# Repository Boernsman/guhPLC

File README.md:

# nymea PLC
The purpose was to design a smart home server that runns guhIO and is especially fittet to the needs of single-family house builders. It is the central switching unit that can be mounted into the electrical cabinet.

Please note: guhPLC is the abbreviation for 'guh' programmable logic controller. The smart home server has no powerline interface yet.

The layout is not yet tested - no warranty for functionality

	Copyright guh GmbH 2015-2019.

	This documentation describes Open Hardware and is licensed under the CERN OHL v. 1.2.

	You may redistribute and modify this documentation under the terms of the CERN OHL v.1.2. (http://ohwr.org/cernohl).
	
	This documentation is distributed WITHOUT ANY EXPRESS OR IMPLIED WARRANTY, INCLUDING OF MERCHANTABILITY,
	SATISFACTORY QUALITY AND FITNESS FOR A PARTICULAR PURPOSE. Please see the CERN OHL v.1.2 for applicable conditions

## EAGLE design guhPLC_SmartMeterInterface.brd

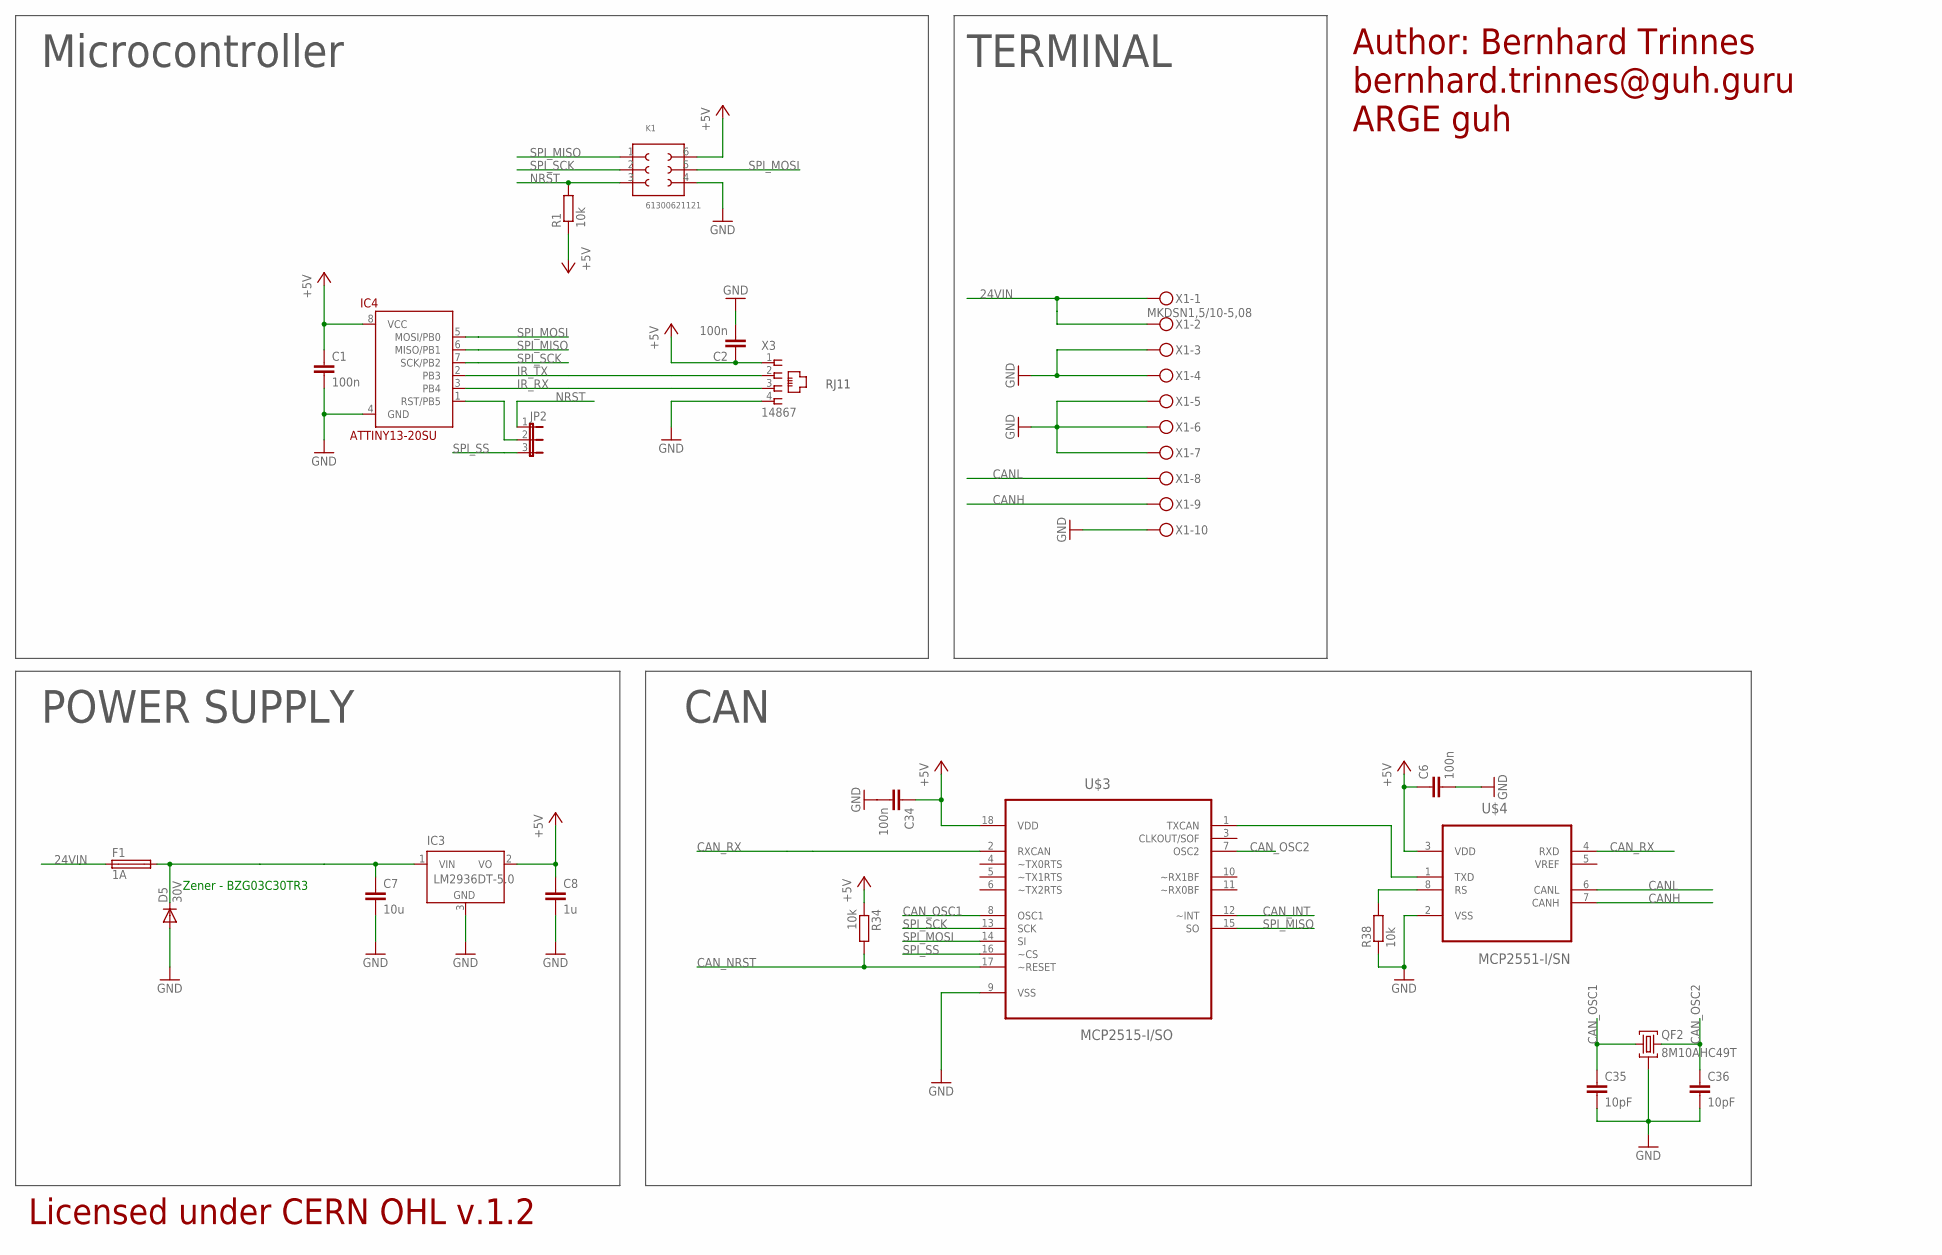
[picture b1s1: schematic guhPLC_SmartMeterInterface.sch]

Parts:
C1, C2, C6, C34: 100n; C0603
C7: 10u; C1206
C8: 1u; C0603
C35, C36: 10pF; C0603
D5: 30V; DO214AC
F1: 1A; LITTLEFUSE
IC3: LM2936DT-5.0; TO252
IC4: ATTINY13-20SU; SOIC8
JP2: JP2E; JP2
K1: 61300621121
QF2: 8M10AHC49T; HC49U
R1, R34, R38: 10k; R0603
U$3: MCP2515-I/SO; SOIC127P1034X264-18N
U$4: MCP2551-I/SN; SOIC127P600X175-8N
X1: MKDSN1,5/10-5,08
X3: 14867

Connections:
24VIN: F1.1, X1.1, X1.2
+5V: C1.1, C2.1, C6.1, C8.1, C34.1, IC3.2 (VO), IC4.8 (VCC), K1.6, R1.1, R34.1, U$3.18 (VDD), U$4.3 (VDD), X3.1
CANH: U$4.7 (CANH), X1.9
CANL: U$4.6 (CANL), X1.8
CAN_INT: U$3.12 (~INT)
CAN_NRST: R34.2, U$3.17 (~RESET)
CAN_OSC1: C35.1, QF2.1, U$3.8 (OSC1)
CAN_OSC2: C36.1, QF2.3, U$3.7 (OSC2)
CAN_RX: U$3.2 (RXCAN), U$4.4 (RXD)
GND: C1.2, C2.2, C6.2, C7.2, C8.2, C34.2, C35.2, C36.2, D5.A, IC3.3 (GND), IC4.4 (GND), K1.4, QF2.2, R38.1, U$3.9 (VSS), U$4.2 (VSS), X1.3, X1.4, X1.5, X1.6, X1.7, X1.10, X3.4
IR_RX: IC4.3 (PB4), X3.3
IR_TX: IC4.2 (PB3), X3.2
unnamed: IC4.1 (RST/PB5), JP2.2
unnamed: U$3.1 (TXCAN), U$4.1 (TXD)
unnamed: R38.2, U$4.8 (RS)
NRST: JP2.1, K1.3, R1.2
SPI_MISO: IC4.6 (MISO/PB1), K1.1, U$3.15 (SO)
SPI_MOSI: IC4.5 (MOSI/PB0), K1.5, U$3.14 (SI)
SPI_SCK: IC4.7 (SCK/PB2), K1.2, U$3.13 (SCK)
SPI_SS: JP2.3, U$3.16 (~CS)
VCC: C7.1, D5.C, F1.2, IC3.1 (VIN)

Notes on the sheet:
CAN
POWER SUPPLY
Microcontroller
TERMINAL
Author: Bernhard Trinnes
bernhard.trinnes@guh.guru
ARGE guh
Licensed under CERN OHL v.1.2
Zener - BZG03C30TR3
RJ11

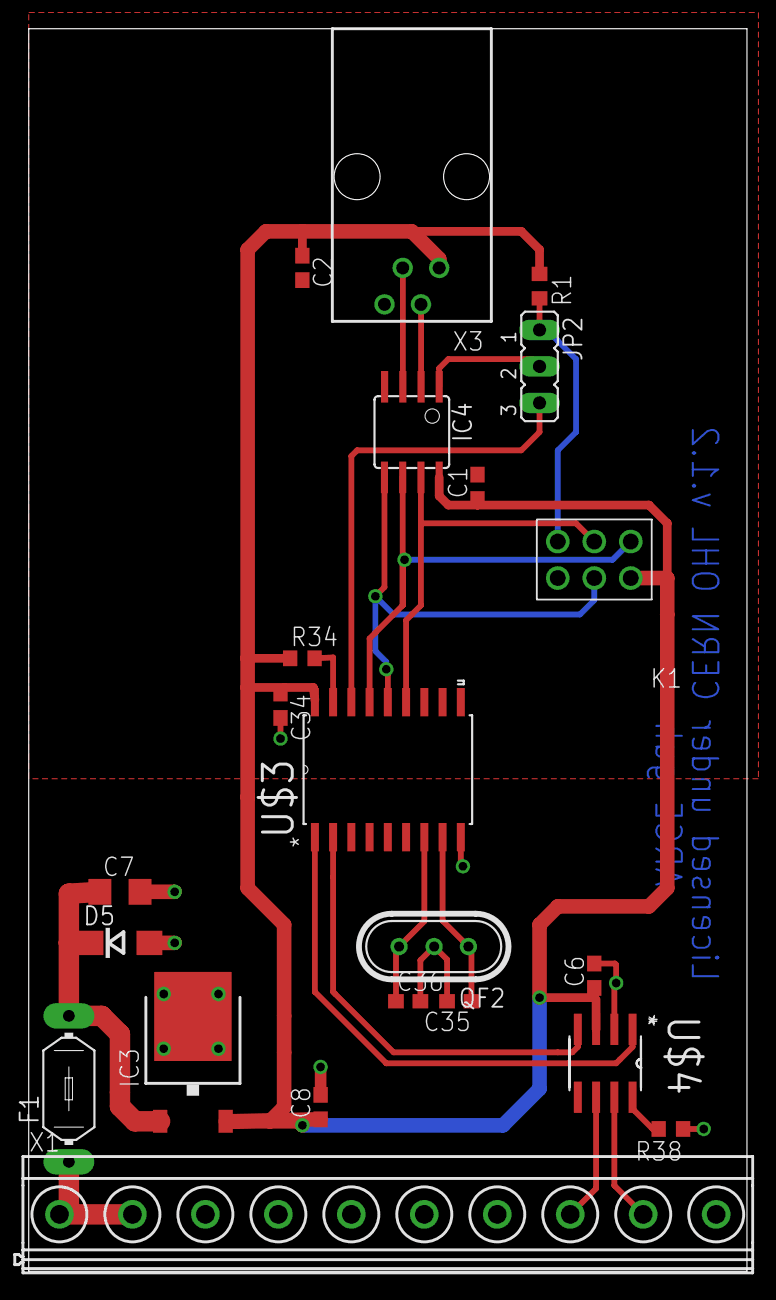
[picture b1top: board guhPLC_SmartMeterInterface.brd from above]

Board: 2 copper layers, 50.0 x 86.5 mm, 22 parts (0 on the bottom side), 20 nets.

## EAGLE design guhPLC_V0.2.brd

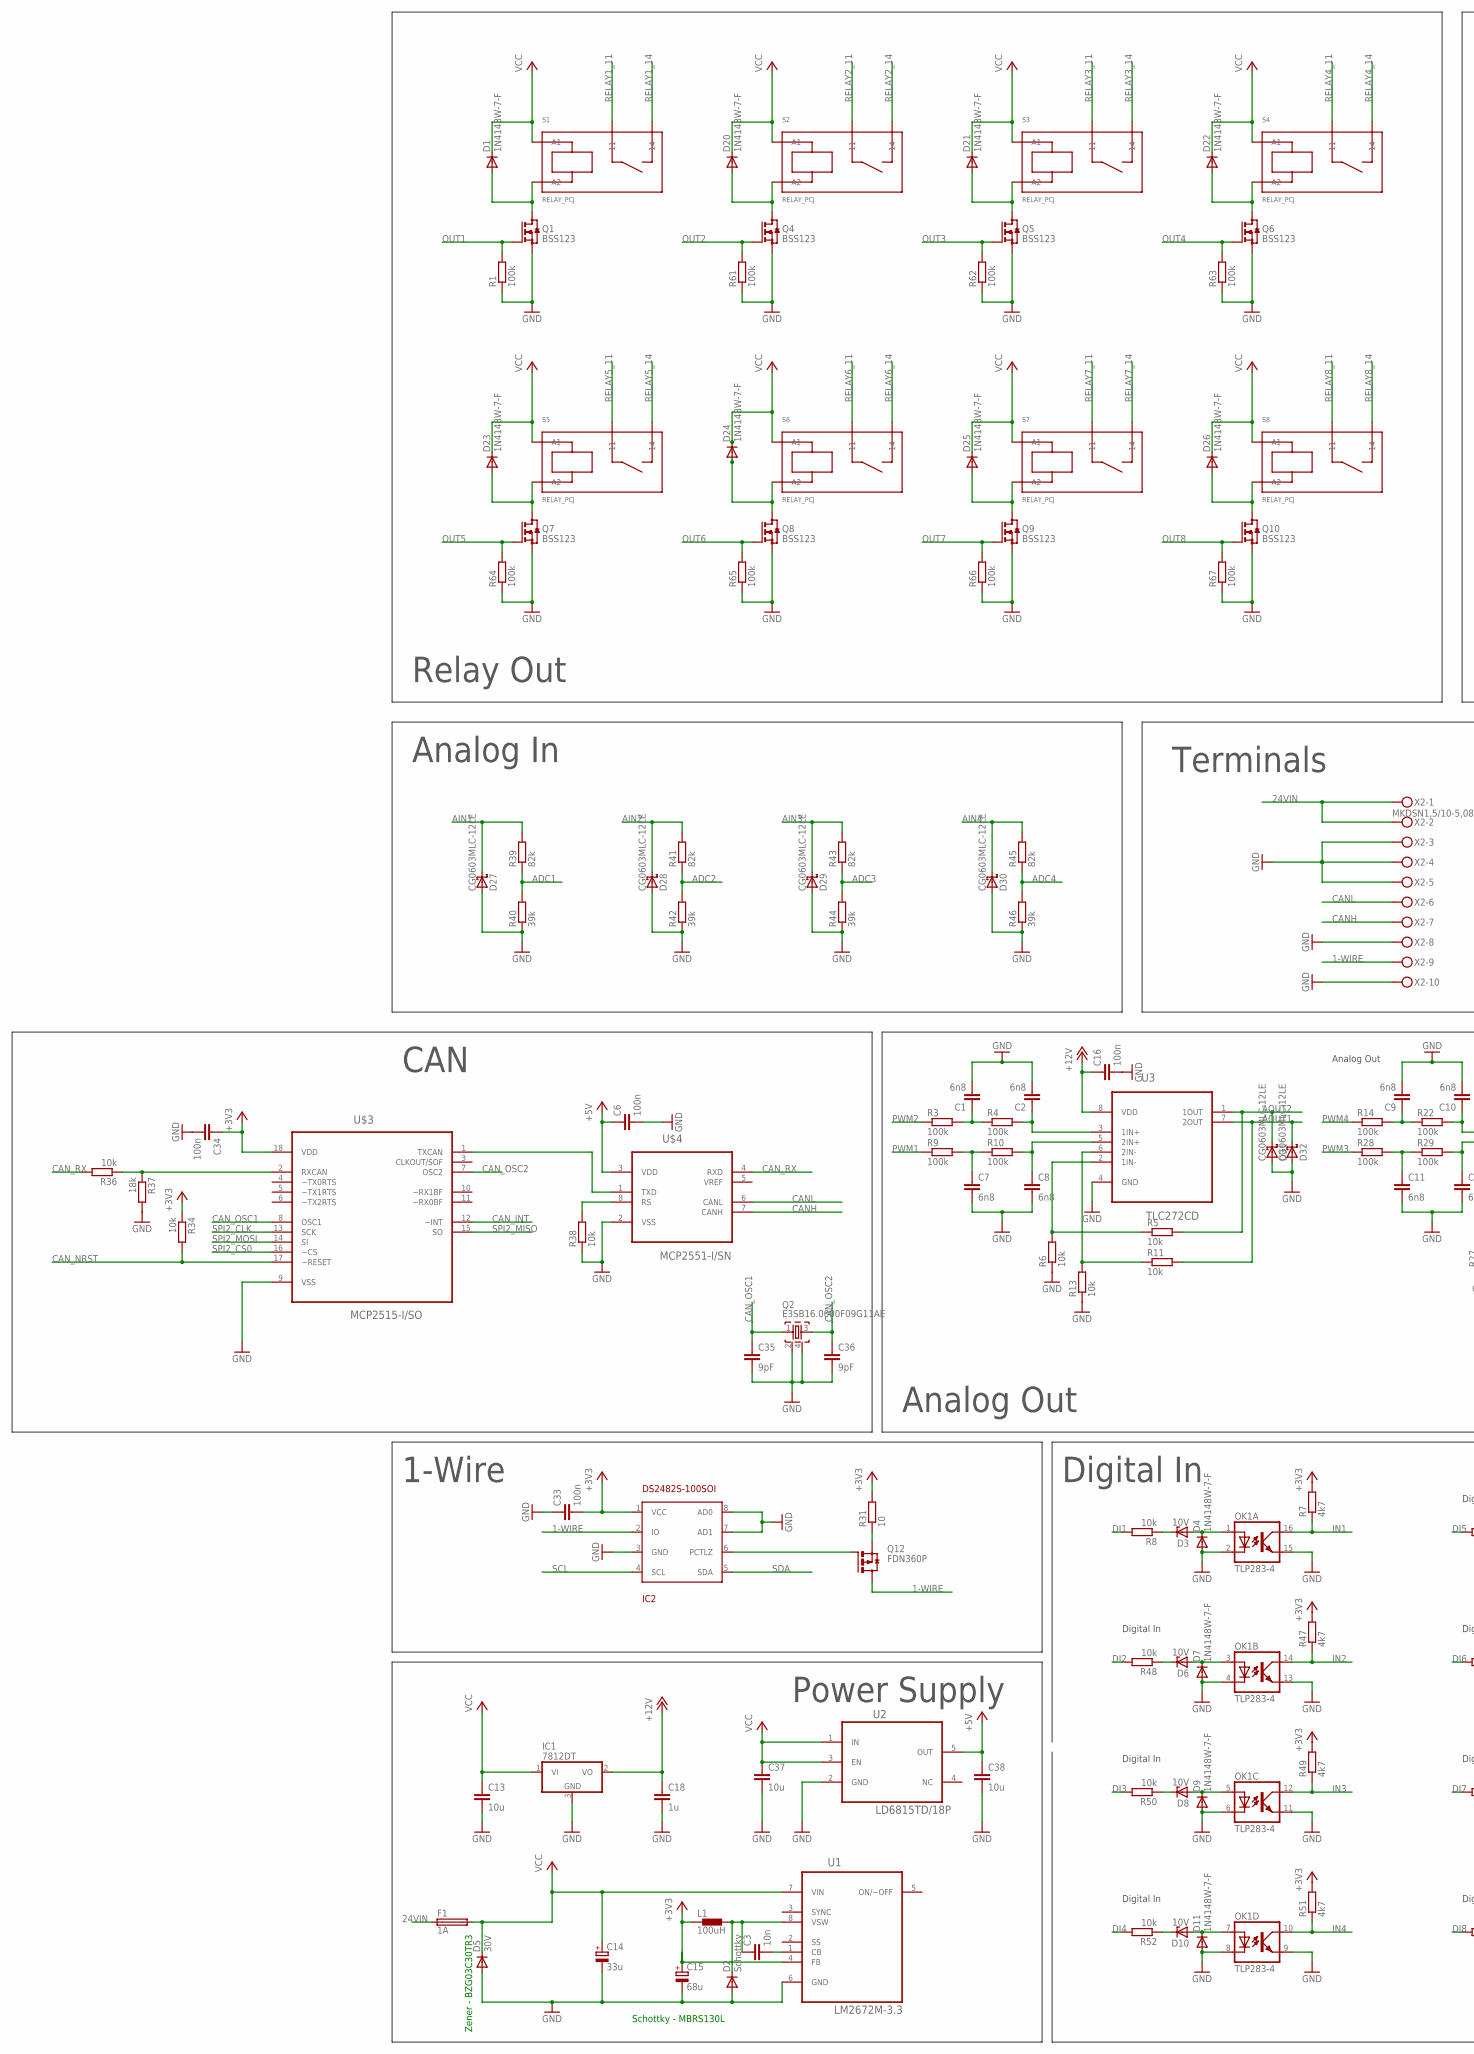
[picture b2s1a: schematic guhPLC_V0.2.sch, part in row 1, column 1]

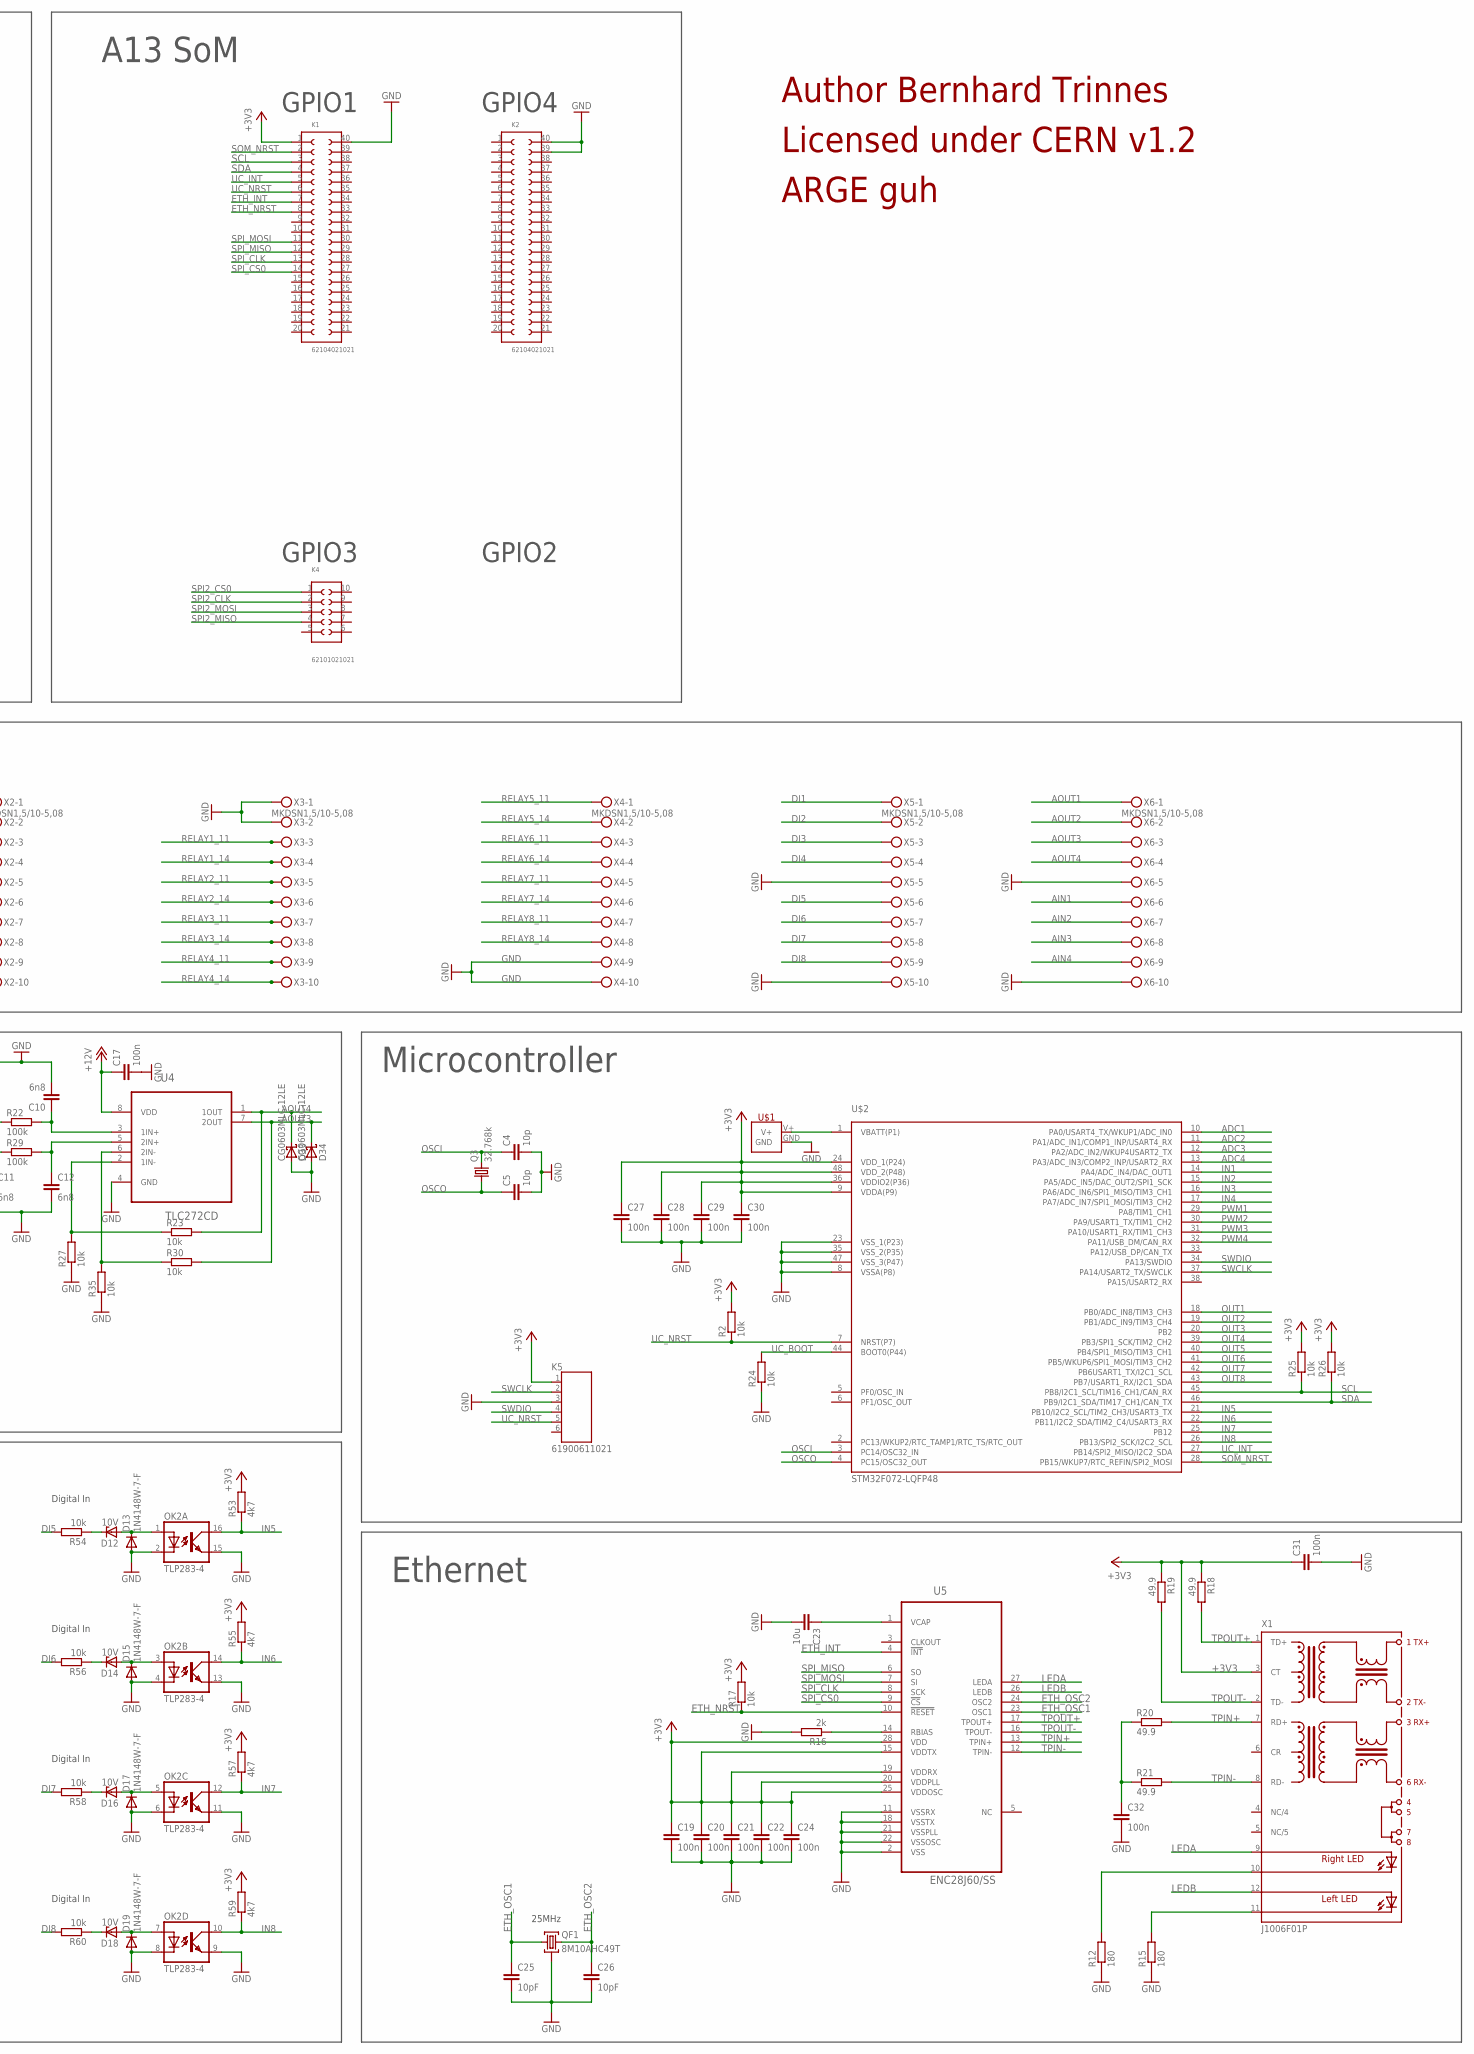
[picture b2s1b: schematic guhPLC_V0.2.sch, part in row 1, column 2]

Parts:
C1, C2, C7, C8, C9, C10, C11, C12: 6n8; C0603
C3: 10n; C0603
C4, C5: 10p; C0603
C6, C16, C17, C19, C20, C21, C22, C24, C27, C28, C29, C30, C31, C33, C34: 100n; C0603
C13, C37, C38: 10u; C1206
C14: 33u; CT7343
C15: 68u; CT6032
C18: 1u; C1206
C23: 10u; C0603
C25, C26: 10pF; C0603
C32: 100n; C0402
C35, C36: 9pF; C0603
D1, D4, D7, D9, D11, D13, D15, D17, D19, D20, D21, D22, D23, D24, D25, D26: 1N4148W-7-F; SOD123
D2: Schottky; DO214AA
D3, D6, D8, D10, D12, D14, D16, D18: 10V; SOD80C
D5: 30V; DO214AC
D27, D28, D29, D30, D31, D32, D33, D34: CG0603MLC-12LE; R0603
F1: 1A; LITTLEFUSE
IC1: 7812DT; TO252
IC2: DS2482S-100SOI; SOIC127P600X175-8N
K1, K2: 62104021021
K4: 62101021021
K5: 61900611021
L1: 100uH; DR1030
OK1, OK2: TLP283-4; MINI-FLAT-16
Q1, Q4, Q5, Q6, Q7, Q8, Q9, Q10: BSS123; SOT23
Q2: E3SB16.0000F09G11AE; E3SBXXXXXXXF09G11AE
Q3: 32.768k; TC26H
Q12: FDN360P; SUPER-SOT3
QF1: 8M10AHC49T; HC49U
R1, R3, R4, R9, R10, R14, R22, R28, R29, R61, R62, R63, R64, R65, R66, R67: 100k; R0603
R2, R17, R24, R25, R26, R34, R36, R38: 10k; R0603
R5, R6, R8, R11, R13, R23, R27, R30, R35, R48, R50, R52, R54, R56, R58, R60: 10k; R0805
R7, R47, R49, R51, R53, R55, R57, R59: 4k7; R0603
R12, R15: 180; R0603
R16: 2k; R0603
R18, R19, R20, R21: 49.9; R0603
R31: 10; R0805
R37: 18k; R0603
R39, R41, R43, R45: 82k; R0805
R40, R42, R44, R46: 39k; R0805
S1, S2, S3, S4, S5, S6, S7, S8: RELAY_PCJ
U1: LM2672M-3.3; SOIC127P600X175-8N
U2: LD6815TD/18P; SOT95P275X110-5N
U3, U4: TLC272CD; SOIC127P600X175-8N
U5: ENC28J60/SS; SOP65P780X200-28N
U$1: MULTICOMP-CH7410-2032LF
U$2: STM32F072-LQFP48; LQFP48
U$3: MCP2515-I/SO; SOIC127P1034X264-18N
U$4: MCP2551-I/SN; SOIC127P600X175-8N
X1: J1006F01P; J1
X2, X3, X4, X5, X6: MKDSN1,5/10-5,08

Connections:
1-WIRE: IC2.2 (IO), Q12.3 (D), X2.9
24VIN: F1.1, X2.1, X2.2
+3V3: C15.+, C19.1, C20.1, C21.1, C22.1, C24.1, C27.1, C28.1, C29.1, C30.1, C31.1, C33.2, C34.1, IC2.1 (VCC), K1.1, K5.1, L1.1, R2.2, R7.2, R17.2, R18.1, R19.1, R25.2, R26.2, R31.2, R34.1, R47.2, R49.2, R51.2, R53.2, R55.2, R57.2, R59.2, U1.4 (FB), U5.15 (VDDTX), U5.19 (VDDRX), U5.20 (VDDPLL), U5.25 (VDDOSC), U5.28 (VDD), U$2.9 (VDDA(P9)), U$2.24 (VDD_1(P24)), U$2.36 (VDDIO2(P36)), U$2.48 (VDD_2(P48)), U$3.18 (VDD), X1.3 (CT)
+5V: C6.1, C38.1, U2.5 (OUT), U$4.3 (VDD)
+12V: C16.1, C17.1, C18.1, IC1.2 (VO), U3.8 (VDD), U4.8 (VDD)
ADC1: R39.1, R40.2, U$2.10 (PA0/USART4_TX/WKUP1/ADC_IN0)
ADC2: R41.1, R42.2, U$2.11 (PA1/ADC_IN1/COMP1_INP/USART4_RX)
ADC3: R43.1, R44.2, U$2.12 (PA2/ADC_IN2/WKUP4USART2_TX)
ADC4: R45.1, R46.2, U$2.13 (PA3/ADC_IN3/COMP2_INP/USART2_RX)
AIN1: D27.2 (C), R39.2, X6.6
AIN2: D28.2 (C), R41.2, X6.7
AIN3: D29.2 (C), R43.2, X6.8
AIN4: D30.2 (C), R45.2, X6.9
AOUT1: D32.2 (C), R11.2, U3.7 (2OUT), X6.1
AOUT2: D31.2 (C), R5.2, U3.1 (1OUT), X6.2
AOUT3: D34.2 (C), R30.2, U4.7 (2OUT), X6.3
AOUT4: D33.2 (C), R23.2, U4.1 (1OUT), X6.4
CANH: U$4.7 (CANH), X2.7
CANL: U$4.6 (CANL), X2.6
CAN_INT: U$3.12 (~INT)
CAN_NRST: R34.2, U$3.17 (~RESET)
CAN_OSC1: C35.1, Q2.1, U$3.8 (OSC1)
CAN_OSC2: C36.1, Q2.3, U$3.7 (OSC2)
CAN_RX: R36.2, U$4.4 (RXD)
DI1: R8.2, X5.1
DI2: R48.2, X5.2
DI3: R50.2, X5.3
DI4: R52.2, X5.4
DI5: R54.2, X5.6
DI6: R56.2, X5.7
DI7: R58.2, X5.8
DI8: R60.2, X5.9
ETH_INT: K1.7, U5.4 (!INT)
ETH_NRST: K1.8, R17.1, U5.10 (!RESET)
ETH_OSC1: C25.1, QF1.1, U5.23 (OSC1)
ETH_OSC2: C26.1, QF1.3, U5.24 (OSC2)
GND: C1.2, C2.2, C4.2, C5.2, C6.2, C7.2, C8.2, C9.2, C10.2, C11.2, C12.2, C13.2, C14.-, C15.-, C16.2, C17.2, C18.2, C19.2, C20.2, C21.2, C22.2, C23.2, C24.2, C25.2, C26.2, C27.2, C28.2, C29.2, C30.2, C31.2, C32.2, C33.1, C34.2, C35.2, C36.2, C37.2, C38.2, D2.A, D4.A, D5.A, D7.A, D9.A, D11.A, D13.A, D15.A, D17.A, D19.A, D27.1 (A), D28.1 (A), D29.1 (A), D30.1 (A), D31.1 (A), D32.1 (A), D33.1 (A), D34.1 (A), IC1.3 (GND), IC2.3 (GND), IC2.7 (AD1), IC2.8 (AD0), K1.40, K2.39, K2.40, K5.3, OK1.2 (C), OK1.4 (C), OK1.6 (C), OK1.8 (C), OK1.9 (EMIT), OK1.11 (EMIT), OK1.13 (EMIT), OK1.15 (EMIT), OK2.2 (C), OK2.4 (C), OK2.6 (C), OK2.8 (C), OK2.9 (EMIT), OK2.11 (EMIT), OK2.13 (EMIT), OK2.15 (EMIT), Q1.2 (S), Q2.2, Q2.4, Q4.2 (S), Q5.2 (S), Q6.2 (S), Q7.2 (S), Q8.2 (S), Q9.2 (S), Q10.2 (S), QF1.2, R1.1, R6.1, R12.1, R13.1, R15.1, R16.2, R24.1, R27.1, R35.1, R37.2, R38.1, R40.1, R42.1, R44.1, R46.1, R61.1, R62.1, R63.1, R64.1, R65.1, R66.1, R67.1, U1.6 (GND), U2.2 (GND), U3.4 (GND), U4.4 (GND), U5.2 (VSS), U5.11 (VSSRX), U5.18 (VSSTX), U5.21 (VSSPLL), U5.22 (VSSOSC), U$1.GND, U$2.8 (VSSA(P8)), U$2.23 (VSS_1(P23)), U$2.35 (VSS_2(P35)), U$2.47 (VSS_3(P47)), U$3.9 (VSS), U$4.2 (VSS), X2.3, X2.4, X2.5, X2.8, X2.10, X3.1, X3.2, X4.9, X4.10, X5.5, X5.10, X6.5, X6.10
IN1: OK1.16 (COL), R7.1, U$2.14 (PA4/ADC_IN4/DAC_OUT1)
IN2: OK1.14 (COL), R47.1, U$2.15 (PA5/ADC_IN5/DAC_OUT2/SPI1_SCK)
IN3: OK1.12 (COL), R49.1, U$2.16 (PA6/ADC_IN6/SPI1_MISO/TIM3_CH1)
IN4: OK1.10 (COL), R51.1, U$2.17 (PA7/ADC_IN7/SPI1_MOSI/TIM3_CH2)
IN5: OK2.16 (COL), R53.1, U$2.21 (PB10/I2C2_SCL/TIM2_CH3/USART3_TX)
IN6: OK2.14 (COL), R55.1, U$2.22 (PB11/I2C2_SDA/TIM2_C4/USART3_RX)
IN7: OK2.12 (COL), R57.1, U$2.25 (PB12)
IN8: OK2.10 (COL), R59.1, U$2.26 (PB13/SPI2_SCK/I2C2_SCL)
LEDA: U5.27 (LEDA), X1.9 (A-R)
LEDB: U5.26 (LEDB), X1.12 (A-L)
unnamed: C3.2, U1.1 (CB)
unnamed: IC2.6 (PCTLZ), Q12.1 (G)
unnamed: U$1.V+, U$2.1 (VBATT(P1))
unnamed: D1.A, Q1.3 (D), S1.A2
unnamed: C7.1, R9.2, R10.1
unnamed: C1.1, R3.2, R4.1
unnamed: C2.1, R4.2, U3.3 (1IN+)
unnamed: D3.C, R8.1
unnamed: R5.1, R6.2, U3.2 (1IN-)
unnamed: D3.A, D4.C, OK1.1 (A)
unnamed: C8.1, R10.2, U3.5 (2IN+)
unnamed: D24.A, Q8.3 (D), S6.A2
unnamed: C9.1, R14.2, R22.1
unnamed: C10.1, R22.2, U4.3 (1IN+)
unnamed: R23.1, R27.2, U4.2 (1IN-)
unnamed: C3.1, D2.C, L1.2, U1.8 (VSW)
unnamed: C11.1, R28.2, R29.1
unnamed: C12.1, R29.2, U4.5 (2IN+)
unnamed: Q12.2 (S), R31.1
unnamed: U$3.1 (TXCAN), U$4.1 (TXD)
unnamed: D6.C, R48.1
unnamed: R36.1, R37.1, U$3.2 (RXCAN)
unnamed: D6.A, D7.C, OK1.3 (A)
unnamed: R38.2, U$4.8 (RS)
unnamed: C32.1, R20.1, R21.1
unnamed: C23.1, U5.1 (VCAP)
unnamed: R12.2, X1.10 (C-R)
unnamed: R15.2, X1.11 (C-L)
unnamed: R11.1, R13.2, U3.6 (2IN-)
unnamed: R30.1, R35.2, U4.6 (2IN-)
unnamed: D8.C, R50.1
unnamed: D8.A, D9.C, OK1.5 (A)
unnamed: D10.C, R52.1
unnamed: D10.A, D11.C, OK1.7 (A)
unnamed: D12.C, R54.1
unnamed: R16.1, U5.14 (RBIAS)
unnamed: D12.A, D13.C, OK2.1 (A)
unnamed: D14.C, R56.1
unnamed: D14.A, D15.C, OK2.3 (A)
unnamed: D16.C, R58.1
unnamed: D16.A, D17.C, OK2.5 (A)
unnamed: D18.C, R60.1
unnamed: D18.A, D19.C, OK2.7 (A)
unnamed: D20.A, Q4.3 (D), S2.A2
unnamed: D21.A, Q5.3 (D), S3.A2
unnamed: D22.A, Q6.3 (D), S4.A2
unnamed: D23.A, Q7.3 (D), S5.A2
unnamed: D25.A, Q9.3 (D), S7.A2
unnamed: D26.A, Q10.3 (D), S8.A2
OSCI: C4.1, Q3.2, U$2.3 (PC14/OSC32_IN)
OSCO: C5.1, Q3.1, U$2.4 (PC15/OSC32_OUT)
OUT1: Q1.1 (G), R1.2, U$2.18 (PB0/ADC_IN8/TIM3_CH3)
OUT2: Q4.1 (G), R61.2, U$2.19 (PB1/ADC_IN9/TIM3_CH4)
OUT3: Q5.1 (G), R62.2, U$2.20 (PB2)
OUT4: Q6.1 (G), R63.2, U$2.39 (PB3/SPI1_SCK/TIM2_CH2)
OUT5: Q7.1 (G), R64.2, U$2.40 (PB4/SPI1_MISO/TIM3_CH1)
OUT6: Q8.1 (G), R65.2, U$2.41 (PB5/WKUP6/SPI1_MOSI/TIM3_CH2)
OUT7: Q9.1 (G), R66.2, U$2.42 (PB6USART1_TX/I2C1_SCL)
OUT8: Q10.1 (G), R67.2, U$2.43 (PB7/USART1_RX/I2C1_SDA)
PWM1: R9.1, U$2.29 (PA8/TIM1_CH1)
PWM2: R3.1, U$2.30 (PA9/USART1_TX/TIM1_CH2)
PWM3: R28.1, U$2.31 (PA10/USART1_RX/TIM1_CH3)
PWM4: R14.1, U$2.32 (PA11/USB_DM/CAN_RX)
RELAY1_11: S1.11, X3.3
RELAY1_14: S1.14, X3.4
RELAY2_11: S2.11, X3.5
RELAY2_14: S2.14, X3.6
RELAY3_11: S3.11, X3.7
RELAY3_14: S3.14, X3.8
RELAY4_11: S4.11, X3.9
RELAY4_14: S4.14, X3.10
RELAY5_11: S5.11, X4.1
RELAY5_14: S5.14, X4.2
RELAY6_11: S6.11, X4.3
RELAY6_14: S6.14, X4.4
RELAY7_11: S7.11, X4.5
RELAY7_14: S7.14, X4.6
RELAY8_11: S8.11, X4.7
RELAY8_14: S8.14, X4.8
SCL: IC2.4 (SCL), K1.3, R25.1, U$2.45 (PB8/I2C1_SCL/TIM16_CH1/CAN_RX)
SDA: IC2.5 (SDA), K1.4, R26.1, U$2.46 (PB9/I2C1_SDA/TIM17_CH1/CAN_TX)
SOM_NRST: K1.2, U$2.28 (PB15/WKUP7/RTC_REFIN/SPI2_MOSI)
SPI2_CLK: K4.2, U$3.13 (SCK)
SPI2_CS0: K4.1, U$3.16 (~CS)
SPI2_MISO: K4.4, U$3.15 (SO)
SPI2_MOSI: K4.3, U$3.14 (SI)
SPI_CLK: K1.13, U5.8 (SCK)
SPI_CS0: K1.14, U5.9 (!CS)
SPI_MISO: K1.12, U5.6 (SO)
SPI_MOSI: K1.11, U5.7 (SI)
SWCLK: K5.2, U$2.37 (PA14/USART2_TX/SWCLK)
SWDIO: K5.4, U$2.34 (PA13/SWDIO)
TPIN+: R20.2, U5.13 (TPIN+), X1.7 (RD+)
TPIN-: R21.2, U5.12 (TPIN-), X1.8 (RD-)
TPOUT+: R18.2, U5.17 (TPOUT+), X1.1 (TD+)
TPOUT-: R19.2, U5.16 (TPOUT-), X1.2 (TD-)
UC_BOOT: R24.2, U$2.44 (BOOT0(P44))
UC_INT: K1.5, U$2.27 (PB14/SPI2_MISO/I2C2_SDA)
UC_NRST: K1.6, K5.5, R2.1, U$2.7 (NRST(P7))
VCC: C13.1, C14.+, C37.1, D1.C, D5.C, D20.C, D21.C, D22.C, D23.C, D24.C, D25.C, D26.C, F1.2, IC1.1 (VI), S1.A1, S2.A1, S3.A1, S4.A1, S5.A1, S6.A1, S7.A1, S8.A1, U1.7 (VIN), U2.1 (IN), U2.3 (EN)

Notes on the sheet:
A13 SoM
Analog Out
Analog In
Digital In
Power Supply
Microcontroller
CAN
Relay Out
GPIO1
GPIO2
GPIO3
GPIO4
Ethernet
25MHz
Terminals
Schottky - MBRS130L
Zener - BZG03C30TR3
Author Bernhard Trinnes
Licensed under CERN v1.2
ARGE guh
1-Wire

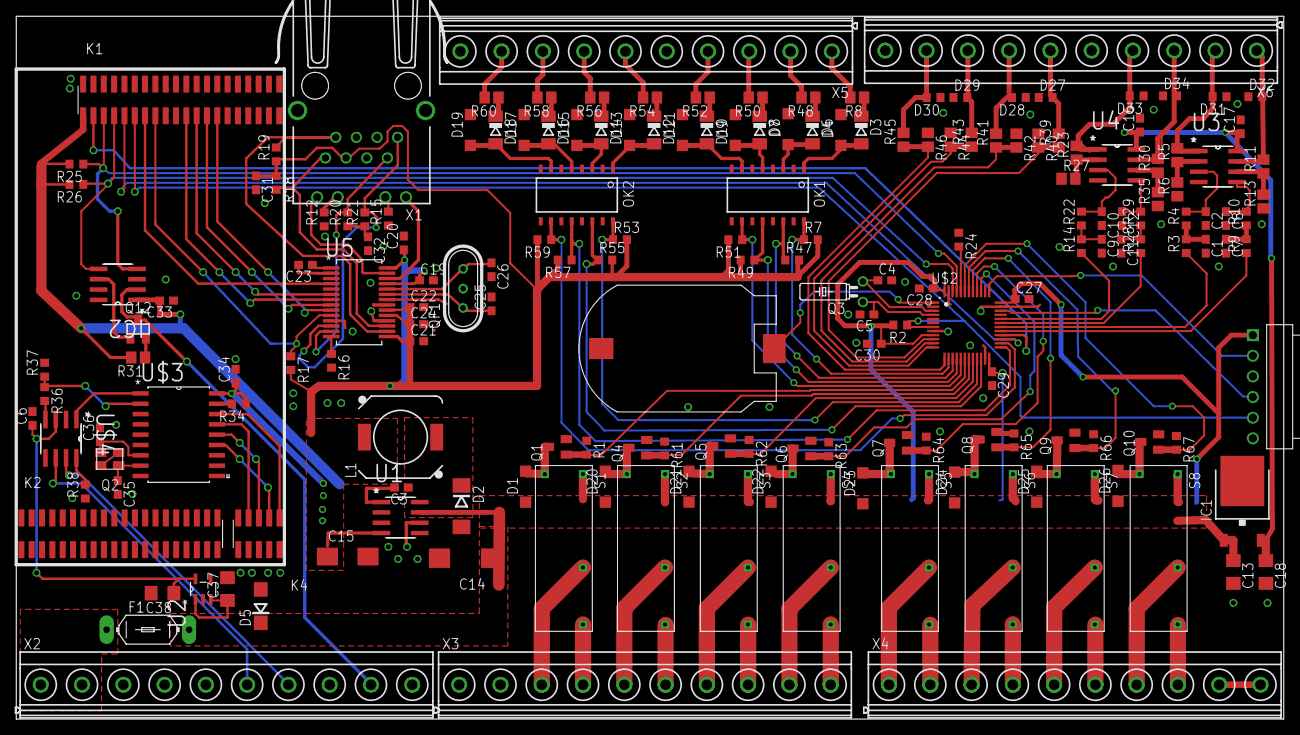
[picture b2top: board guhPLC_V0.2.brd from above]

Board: 2 copper layers, 156.0 x 86.5 mm, 182 parts (0 on the bottom side), 146 nets.

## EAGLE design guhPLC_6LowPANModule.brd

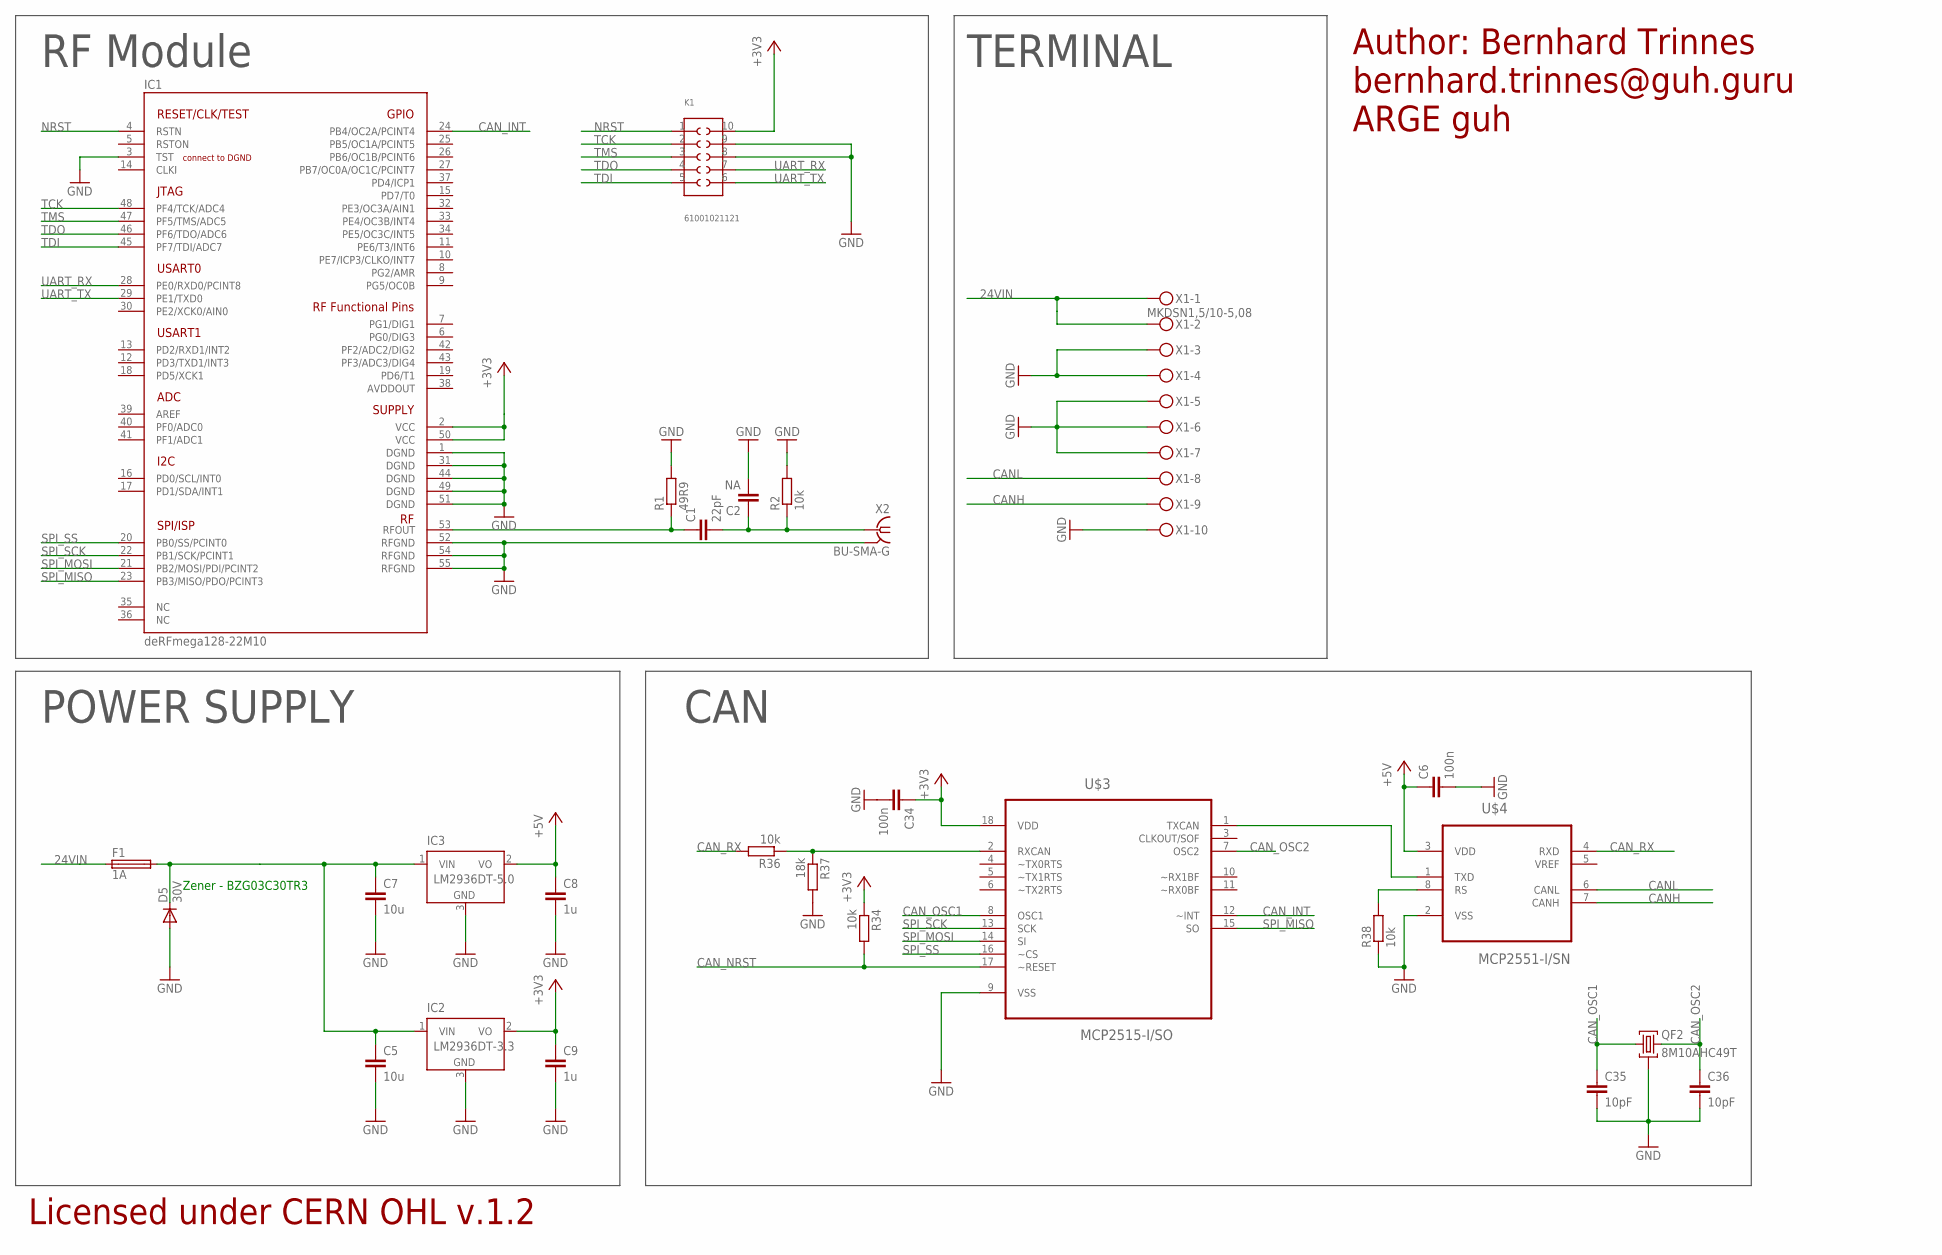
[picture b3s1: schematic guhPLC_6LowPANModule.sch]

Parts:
C1: 22pF; C0402
C2: NA; C0402
C5, C7: 10u; C1206
C6, C34: 100n; C0603
C8, C9: 1u; C0603
C35, C36: 10pF; C0603
D5: 30V; DO214AC
F1: 1A; LITTLEFUSE
IC1: DERFMEGA128-22M10; A-M10
IC2: LM2936DT-3.3; TO252
IC3: LM2936DT-5.0; TO252
K1: 61001021121
QF2: 8M10AHC49T; HC49U
R1: 49R9; R0402
R2: 10k; R0402
R34, R36, R38: 10k; R0603
R37: 18k; R0603
U$3: MCP2515-I/SO; SOIC127P1034X264-18N
U$4: MCP2551-I/SN; SOIC127P600X175-8N
X1: MKDSN1,5/10-5,08
X2: BU-SMA-G

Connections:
24VIN: F1.1, X1.1, X1.2
+3V3: C9.1, C34.1, IC1.2 (VCC), IC1.50 (VCC), IC2.2 (VO), K1.10, R34.1, U$3.18 (VDD)
+5V: C6.1, C8.1, IC3.2 (VO), U$4.3 (VDD)
CANH: U$4.7 (CANH), X1.9
CANL: U$4.6 (CANL), X1.8
CAN_INT: IC1.24 (PB4/OC2A/PCINT4), U$3.12 (~INT)
CAN_NRST: R34.2, U$3.17 (~RESET)
CAN_OSC1: C35.1, QF2.1, U$3.8 (OSC1)
CAN_OSC2: C36.1, QF2.3, U$3.7 (OSC2)
CAN_RX: R36.2, U$4.4 (RXD)
GND: C2.2, C5.2, C6.2, C7.2, C8.2, C9.2, C34.2, C35.2, C36.2, D5.A, IC1.1 (DGND), IC1.3 (TST), IC1.31 (DGND), IC1.44 (DGND), IC1.49 (DGND), IC1.51 (DGND), IC1.52 (RFGND), IC1.54 (RFGND), IC1.55 (RFGND), IC2.3 (GND), IC3.3 (GND), K1.8, K1.9, QF2.2, R1.2, R2.2, R37.2, R38.1, U$3.9 (VSS), U$4.2 (VSS), X1.3, X1.4, X1.5, X1.6, X1.7, X1.10, X2.2 (GND), X2.3 (GND), X2.4 (GND), X2.5 (GND)
unnamed: C1.2, C2.1, R2.1, X2.1
unnamed: U$3.1 (TXCAN), U$4.1 (TXD)
unnamed: R36.1, R37.1, U$3.2 (RXCAN)
unnamed: R38.2, U$4.8 (RS)
NRST: IC1.4 (RSTN), K1.1
RFOUT: C1.1, IC1.53 (RFOUT), R1.1
SPI_MISO: IC1.23 (PB3/MISO/PDO/PCINT3), U$3.15 (SO)
SPI_MOSI: IC1.21 (PB2/MOSI/PDI/PCINT2), U$3.14 (SI)
SPI_SCK: IC1.22 (PB1/SCK/PCINT1), U$3.13 (SCK)
SPI_SS: IC1.20 (PB0/SS/PCINT0), U$3.16 (~CS)
TCK: IC1.48 (PF4/TCK/ADC4), K1.2
TDI: IC1.45 (PF7/TDI/ADC7), K1.5
TDO: IC1.46 (PF6/TDO/ADC6), K1.4
TMS: IC1.47 (PF5/TMS/ADC5), K1.3
UART_RX: IC1.28 (PE0/RXD0/PCINT8), K1.7
UART_TX: IC1.29 (PE1/TXD0), K1.6
VCC: C5.1, C7.1, D5.C, F1.2, IC2.1 (VIN), IC3.1 (VIN)

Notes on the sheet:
CAN
POWER SUPPLY
RF Module
TERMINAL
Author: Bernhard Trinnes
bernhard.trinnes@guh.guru
ARGE guh
Licensed under CERN OHL v.1.2
Zener - BZG03C30TR3

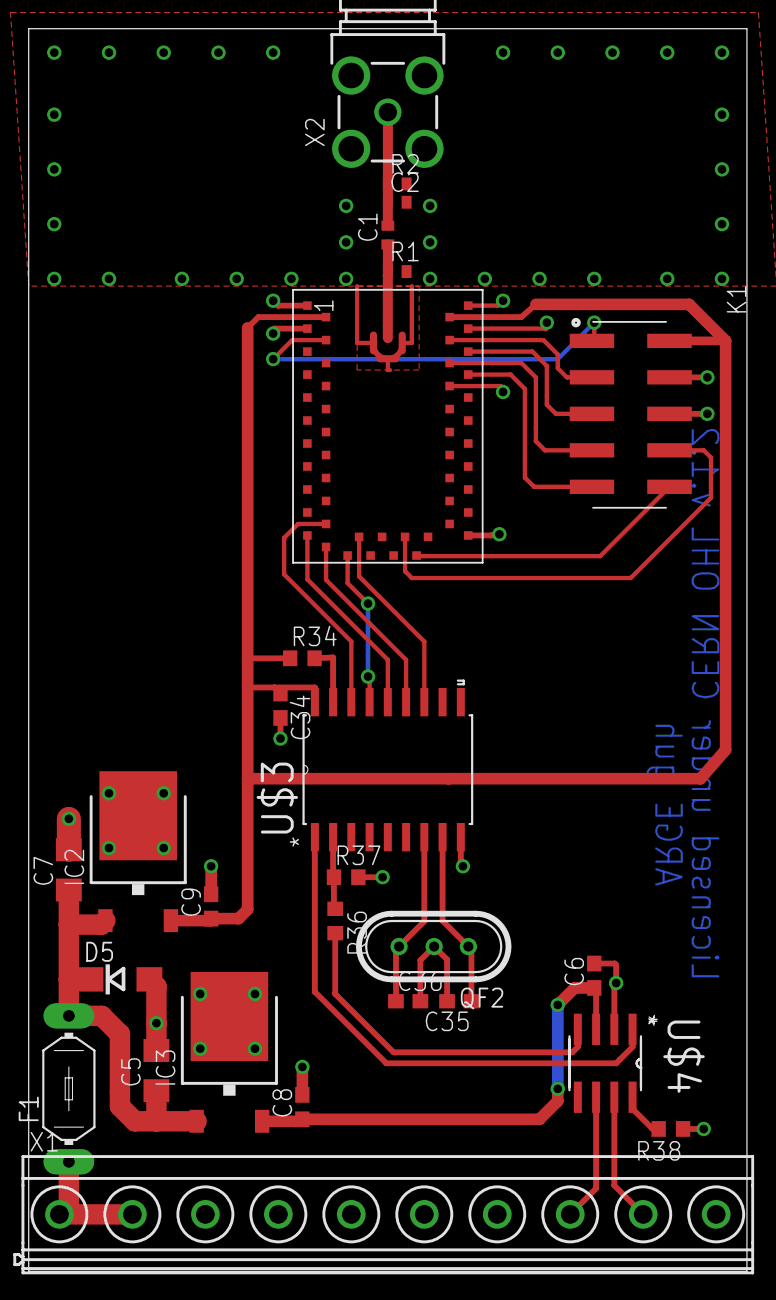
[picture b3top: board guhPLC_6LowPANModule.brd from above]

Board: 2 copper layers, 50.0 x 86.5 mm, 27 parts (0 on the bottom side), 28 nets.

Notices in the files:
parts and their libraries:
EagleLibrary_Wuerth_Elektronik_eiCan_Boa: Copyright: Würth Elektronik
